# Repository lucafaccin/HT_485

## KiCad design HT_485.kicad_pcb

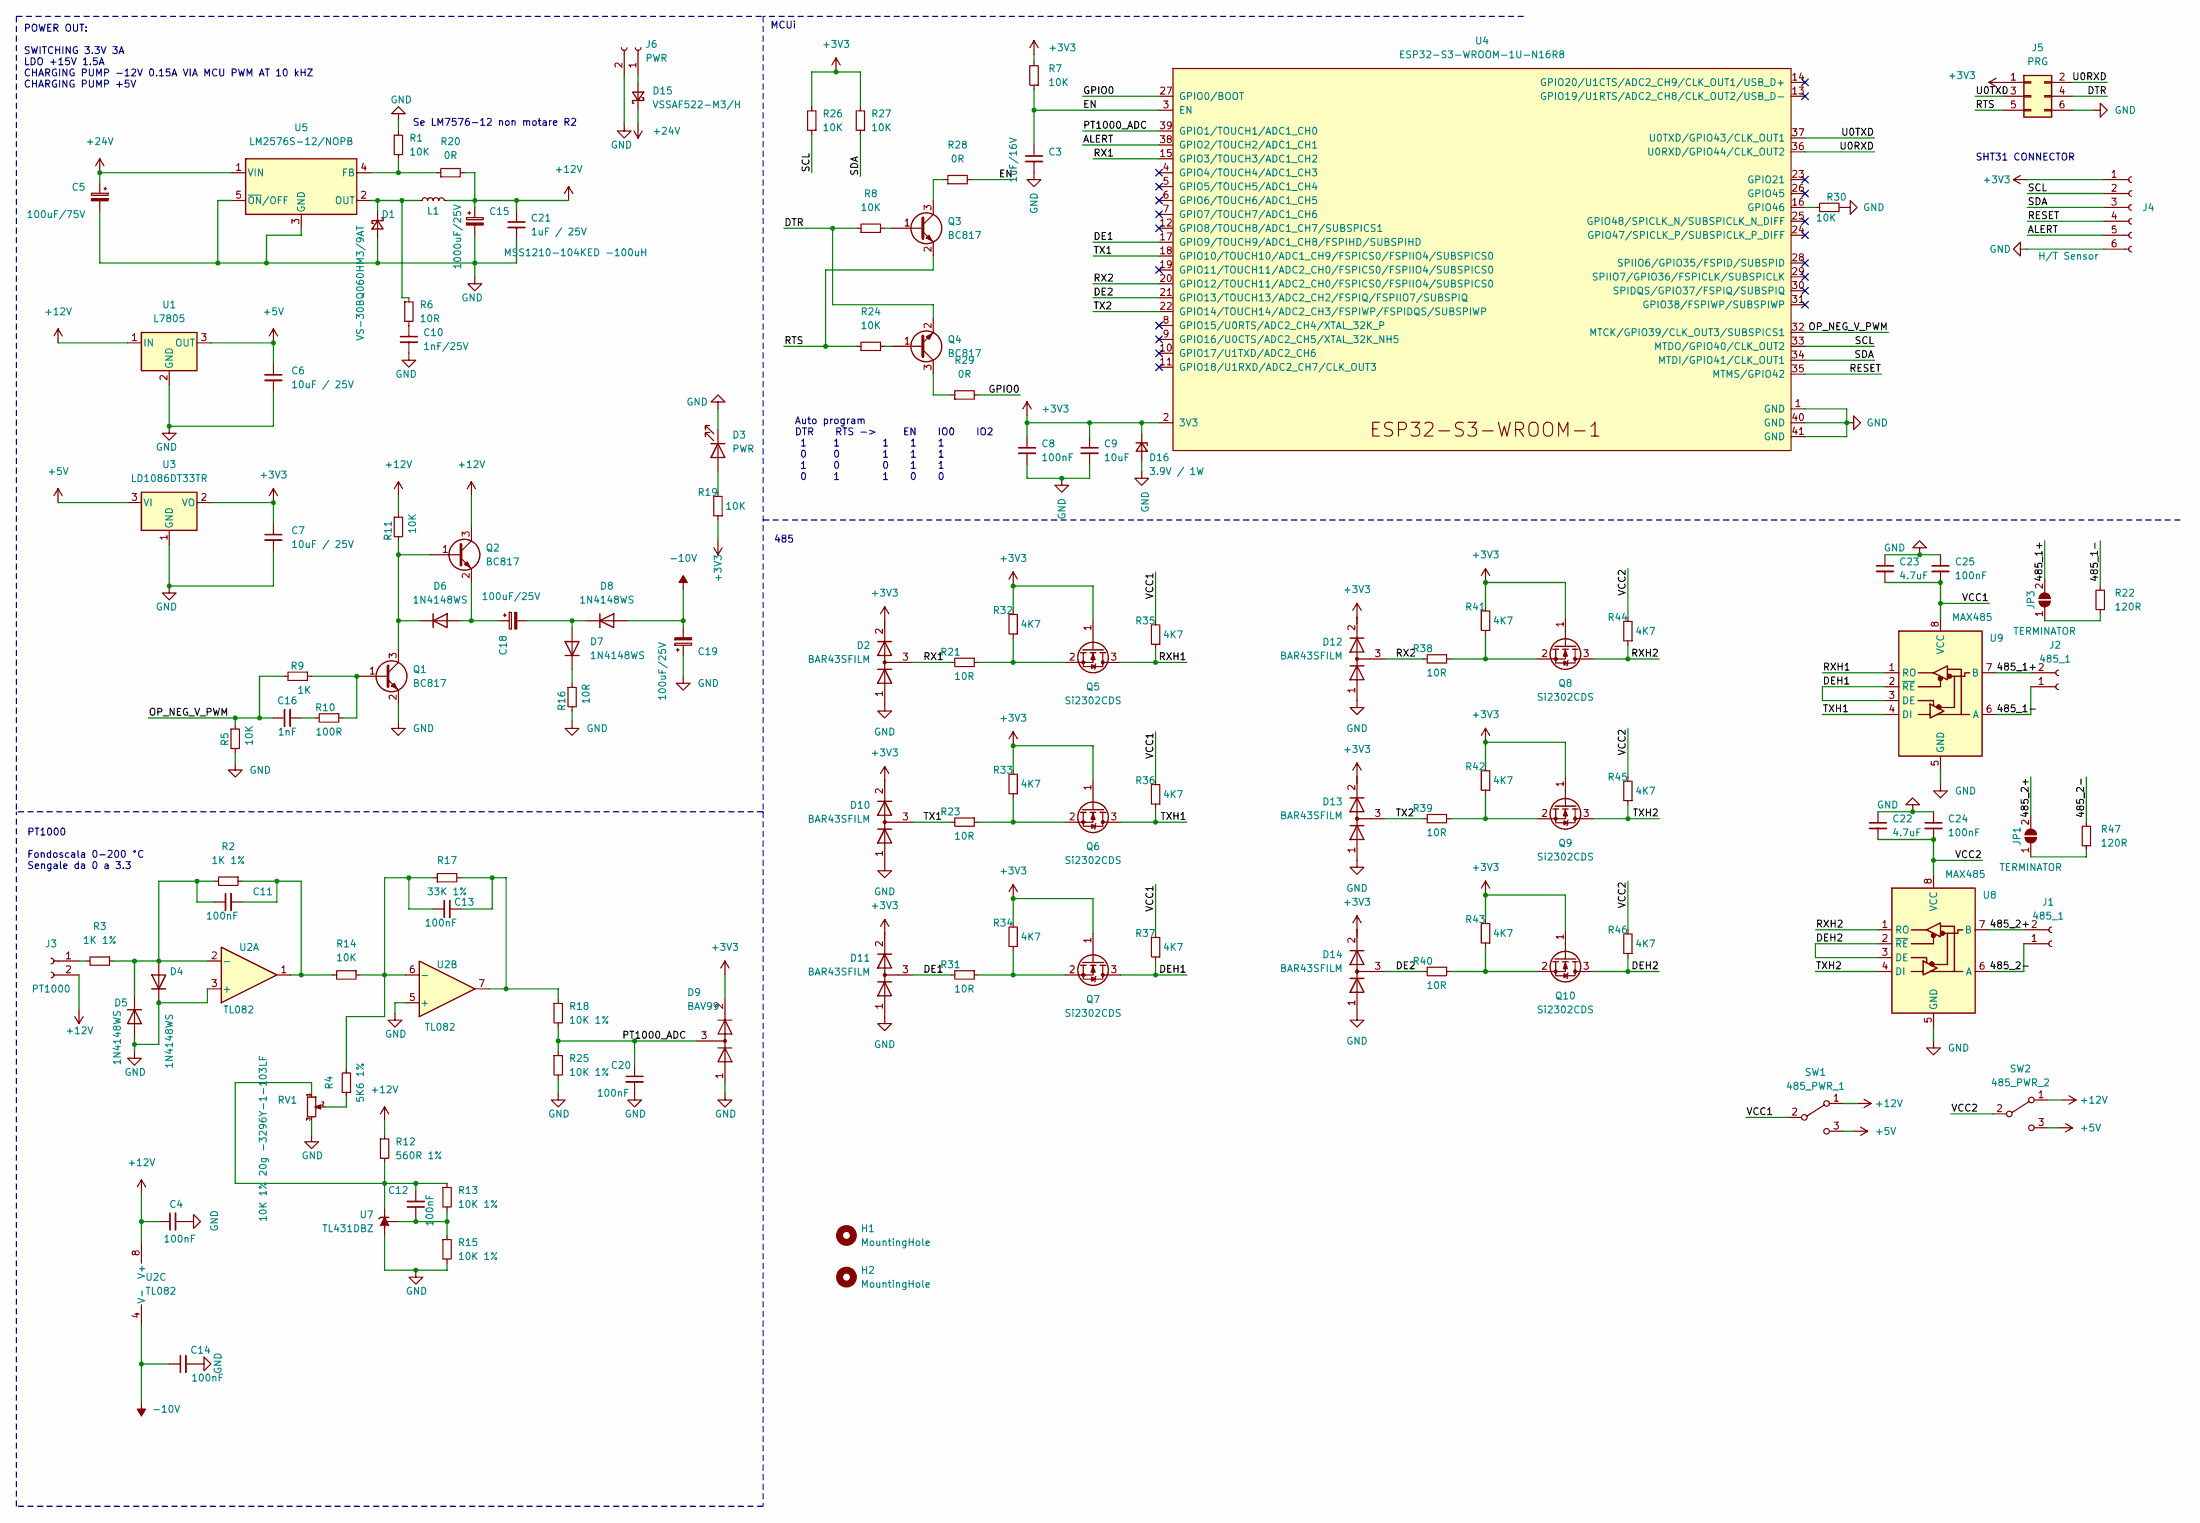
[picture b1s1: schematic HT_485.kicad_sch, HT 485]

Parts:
C3: 1uF/16V; C_0805_2012Metric
C4, C8, C11, C12, C13, C14, C20, C24, C25: 100nF; C_0805_2012Metric
C5: 100uF/75V; CP_Elec_8x10.5
C6, C7: 10uF / 25V; C_0805_2012Metric
C9: 10uF; C_0805_2012Metric
C10: 1nF/25V; C_0805_2012Metric
C15: 1000uF/25V; CP_Elec_10x10.5
C16: 1nF; C_0805_2012Metric
C18, C19: 100uF/25V; CP_Elec_6.3x7.7
C21: 1uF / 25V; C_0805_2012Metric
C22, C23: 4.7uF; C_0805_2012Metric
D1: VS-30BQ060HM3/9AT; D_SMB-SMC_Universal_Handsoldering
D2, D10, D11, D12, D13, D14: BAR43SFILM; SOT-23
D3: PWR; LED_0805_2012Metric
D4, D5, D6, D7, D8: 1N4148WS; D_SOD-323
D9: BAV99; SOT-23
D15: VSSAF522-M3/H; D_SMA-SMB_Universal_Handsoldering
D16: 3.9V / 1W; D_SOD-128
H1, H2: MountingHole; MountingHole_3.2mm_M3
J1, J2: 485_1; TerminalBlock_Phoenix_PT-1,5-2-5.0-H_1x02_P5.00mm_Horizontal
J3: PT1000; TerminalBlock_Phoenix_PT-1,5-2-3.5-H_1x02_P3.50mm_Horizontal
J4: H/T Sensor; JST_PH_S6B-PH-SM4-TB_1x06-1MP_P2.00mm_Horizontal
J5: PRG; PinSocket_2x03_P2.54mm_Vertical
J6: PWR; TerminalBlock_Phoenix_PT-1,5-2-5.0-H_1x02_P5.00mm_Horizontal
JP1, JP3: TERMINATOR; SolderJumper-2_P1.3mm_Open_RoundedPad1.0x1.5mm
L1: MSS1210-104KED -100uH; MSS1210-104KED
Q1, Q2, Q3, Q4: BC817; SOT-23
Q5, Q6, Q7, Q8, Q9, Q10: Si2302CDS; SOT-23
R1, R5, R7, R8, R11, R14, R19, R24, R26, R27, R30: 10K; R_0805_2012Metric_Pad1.20x1.40mm_HandSolder
R2, R3: 1K 1%; R_0805_2012Metric_Pad1.20x1.40mm_HandSolder
R4: 5K6 1%; R_0805_2012Metric_Pad1.20x1.40mm_HandSolder
R6, R16, R21, R23, R31, R38, R39, R40: 10R; R_0805_2012Metric_Pad1.20x1.40mm_HandSolder
R9: 1K; R_0805_2012Metric_Pad1.20x1.40mm_HandSolder
R10: 100R; R_0805_2012Metric_Pad1.20x1.40mm_HandSolder
R12: 560R 1%; R_0805_2012Metric_Pad1.20x1.40mm_HandSolder
R13, R15, R18, R25: 10K 1%; R_0805_2012Metric_Pad1.20x1.40mm_HandSolder
R17: 33K 1%; R_0805_2012Metric_Pad1.20x1.40mm_HandSolder
R20, R28, R29: 0R; R_0805_2012Metric_Pad1.20x1.40mm_HandSolder
R22, R47: 120R; R_0805_2012Metric_Pad1.20x1.40mm_HandSolder
R32, R33, R34, R35, R36, R37, R41, R42, R43, R44, R45, R46: 4K7; R_0805_2012Metric_Pad1.20x1.40mm_HandSolder
RV1: 10K 1% 20g -3296Y-1-103LF; Potentiometer_Bourns_3296Y_Vertical
SW1: 485_PWR_1; PinHeader_1x03_P2.54mm_Vertical
SW2: 485_PWR_2; PinHeader_1x03_P2.54mm_Vertical
U1: L7805; TO-252-3_TabPin2
U2: TL082; SOIC-8-1EP_3.9x4.9mm_P1.27mm_EP2.29x3mm
U3: LD1086DT33TR; TO-252-3_TabPin2
U4: ESP32-S3-WROOM-1U-N16R8; ESP32-S3-WROOM-1
U5: LM2576S-12/NOPB; TO-263-5_TabPin3
U7: TL431DBZ; SOT-23
U8, U9: MAX485; SOIC-8_3.9x4.9mm_P1.27mm

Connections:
+3V3: C7.1, C8.1, C9.1, D2.2 (K), D9.2 (A), D10.2 (K), D11.2 (K), D12.2 (K), D13.2 (K), D14.2 (K), D16.1 (K), J4.1, J5.1, Q5.1 (G), Q6.1 (G), Q7.1 (G), Q8.1 (G), Q9.1 (G), Q10.1 (G), R7.2, R19.1, R26.2, R27.2, R32.2, R33.2, R34.2, R41.2, R42.2, R43.2, U3.2 (VO), U4.2 (3V3)
+5V: C6.1, SW1.3 (C), SW2.3 (C), U1.3 (OUT), U3.3 (VI)
+12V: C4.1, C15.1, C21.1, J3.2, L1.2, Q2.3 (C), R11.1, R12.1, R20.2, SW1.1 (A), SW2.1 (A), U1.1 (IN), U2.8 (V+)
+24V: C5.1, D15.1 (K), U5.1 (VIN)
-10V: C14.1, C19.2, D8.2 (A), U2.4 (V-)
/485_1+: J2.2, JP3.2 (B), U9.7 (B)
/485_1-: J2.1, R22.2, U9.6 (A)
/485_2+: J1.2, JP1.2 (B), U8.7 (B)
/485_2-: J1.1, R47.2, U8.6 (A)
/ALERT: J4.5, U4.38 (GPIO2/TOUCH2/ADC1_CH1)
/DE1: D11.3 (common), R31.2, U4.17 (GPIO9/TOUCH9/ADC1_CH8/FSPIHD/SUBSPIHD)
/DE2: D14.3 (common), R40.2, U4.21 (GPIO13/TOUCH13/ADC2_CH2/FSPIQ/FSPIIO7/S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)
/DEH1: Q7.3 (D), R37.1, U9.2 (~RE), U9.3 (DE)
/DEH2: Q10.3 (D), R46.1, U8.2 (~RE), U8.3 (DE)
/DTR: J5.4, Q4.2 (E), R8.1
/EN: C3.1, R7.1, R28.2, U4.3 (EN)
/GPIO0: R29.2, U4.27 (GPIO0/BOOT)
/OP_NEG_V_PWM: C16.1, R5.1, R9.2, U4.32 (MTCK/GPIO39/CLK_OUT3/SUBSPICS1)
/PT1000_ADC: C20.1, D9.3 (K), R18.2, R25.1, U4.39 (GPIO1/TOUCH1/ADC1_CH0)
/RESET: J4.4, U4.35 (MTMS/GPIO42)
/RTS: J5.5, Q3.2 (E), R24.1
/RX1: D2.3 (common), R21.2, U4.15 (GPIO3/TOUCH3/ADC1_CH2)
/RX2: D12.3 (common), R38.2, U4.20 (GPIO12/TOUCH11/ADC2_CH0/FSPICS0/FSPIIO4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)
/RXH1: Q5.3 (D), R35.1, U9.1 (RO)
/RXH2: Q8.3 (D), R44.1, U8.1 (RO)
/SCL: J4.2, R26.1, U4.33 (MTDO/GPIO40/CLK_OUT2)
/SDA: J4.3, R27.1, U4.34 (MTDI/GPIO41/CLK_OUT1)
/TX1: D10.3 (common), R23.2, U4.18 (GPIO10/TOUCH10/ADC1_CH9/FSPICS0/FSPIIO4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)
/TX2: D13.3 (common), R39.2, U4.22 (GPIO14/TOUCH14/ADC2_CH3/FSPIWP/FSPIDQS/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)
/TXH1: Q6.3 (D), R36.1, U9.4 (DI)
/TXH2: Q9.3 (D), R45.1, U8.4 (DI)
/U0RXD: J5.2, U4.36 (U0RXD/GPIO44/CLK_OUT2)
/U0TXD: J5.3, U4.37 (U0TXD/GPIO43/CLK_OUT1)
/VCC1: C23.2, C25.2, R35.2, R36.2, R37.2, SW1.2 (B), U9.8 (VCC)
/VCC2: C22.2, C24.2, R44.2, R45.2, R46.2, SW2.2 (B), U8.8 (VCC)
GND: C3.2, C4.2, C5.2, C6.2, C7.2, C8.2, C9.2, C10.2, C14.2, C15.2, C19.1, C20.2, C21.2, C22.1, C23.1, C24.1, C25.1, D1.2 (A), D2.1 (A), D3.1 (K), D4.1 (K), D5.2 (A), D9.1 (K), D10.1 (A), D11.1 (A), D12.1 (A), D13.1 (A), D14.1 (A), D16.2 (A), J4.6, J5.6, J6.2, Q1.2 (E), R1.1, R5.2, R15.2, R16.2, R25.2, R30.2, RV1.3, U1.2 (GND), U2.3 (+), U2.5 (+), U3.1 (GND), U4.1 (GND), U4.40 (GND), U4.41 (GND), U5.3 (GND), U5.5 (~ON/OFF), U7.3 (A), U8.5 (GND), U9.5 (GND)
unnamed: C10.1, R6.2
unnamed: C11.2, R2.1, R14.2, U2.1
unnamed: C13.2, R17.2, R18.1, U2.7
unnamed: C16.2, R10.2
unnamed: D1.1 (K), L1.1, R6.1, U5.2 (OUT)
unnamed: D3.2 (A), R19.2
unnamed: C11.1, D4.2 (A), D5.1 (K), R2.2, R3.1, U2.2 (-)
unnamed: C18.1, D6.2 (A), Q2.2 (E)
unnamed: D6.1 (K), Q1.3 (C), Q2.1 (B), R11.2
unnamed: C18.2, D7.2 (A), D8.1 (K)
unnamed: D7.1 (K), R16.1
unnamed: D15.2 (A), J6.1
unnamed: J3.1, R3.2
unnamed: JP1.1 (A), R47.1
unnamed: JP3.1 (A), R22.1
unnamed: Q1.1 (B), R9.1, R10.1
unnamed: Q3.1 (B), R8.2
unnamed: Q3.3 (C), R28.1
unnamed: Q4.1 (B), R24.2
unnamed: Q4.3 (C), R29.1
unnamed: Q5.2 (S), R21.1, R32.1
unnamed: Q6.2 (S), R23.1, R33.1
unnamed: Q7.2 (S), R31.1, R34.1
unnamed: Q8.2 (S), R38.1, R41.1
unnamed: Q9.2 (S), R39.1, R42.1
unnamed: Q10.2 (S), R40.1, R43.1
unnamed: R4.1, RV1.2
unnamed: C13.1, R4.2, R14.1, R17.1, U2.6 (-)
unnamed: R30.1, U4.16 (GPIO46)
unnamed: R1.2, R20.1, U5.4 (FB)
unnamed: C12.2, R12.2, R13.1, RV1.1, U7.1 (K)
unnamed: C12.1, R13.2, R15.1, U7.2 (REF)

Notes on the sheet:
Auto program DTR RTS -> EN IO0 IO2 1 1 1 1 1 0 0 1 1 1 1 0 0 1 1 0 1 1 0 0
485
Se LM7576-12 non motare R2
SHT31 CONNECTOR
MCUì
PT1000 Fondoscala 0-200 °C Sengale da 0 a 3.3
POWER OUT: SWITCHING 3.3V 3A LDO +15V 1.5A CHARGING PUMP -12V 0.15A VIA MCU PWM AT 10 kHZ CHARGING PUMP +5V

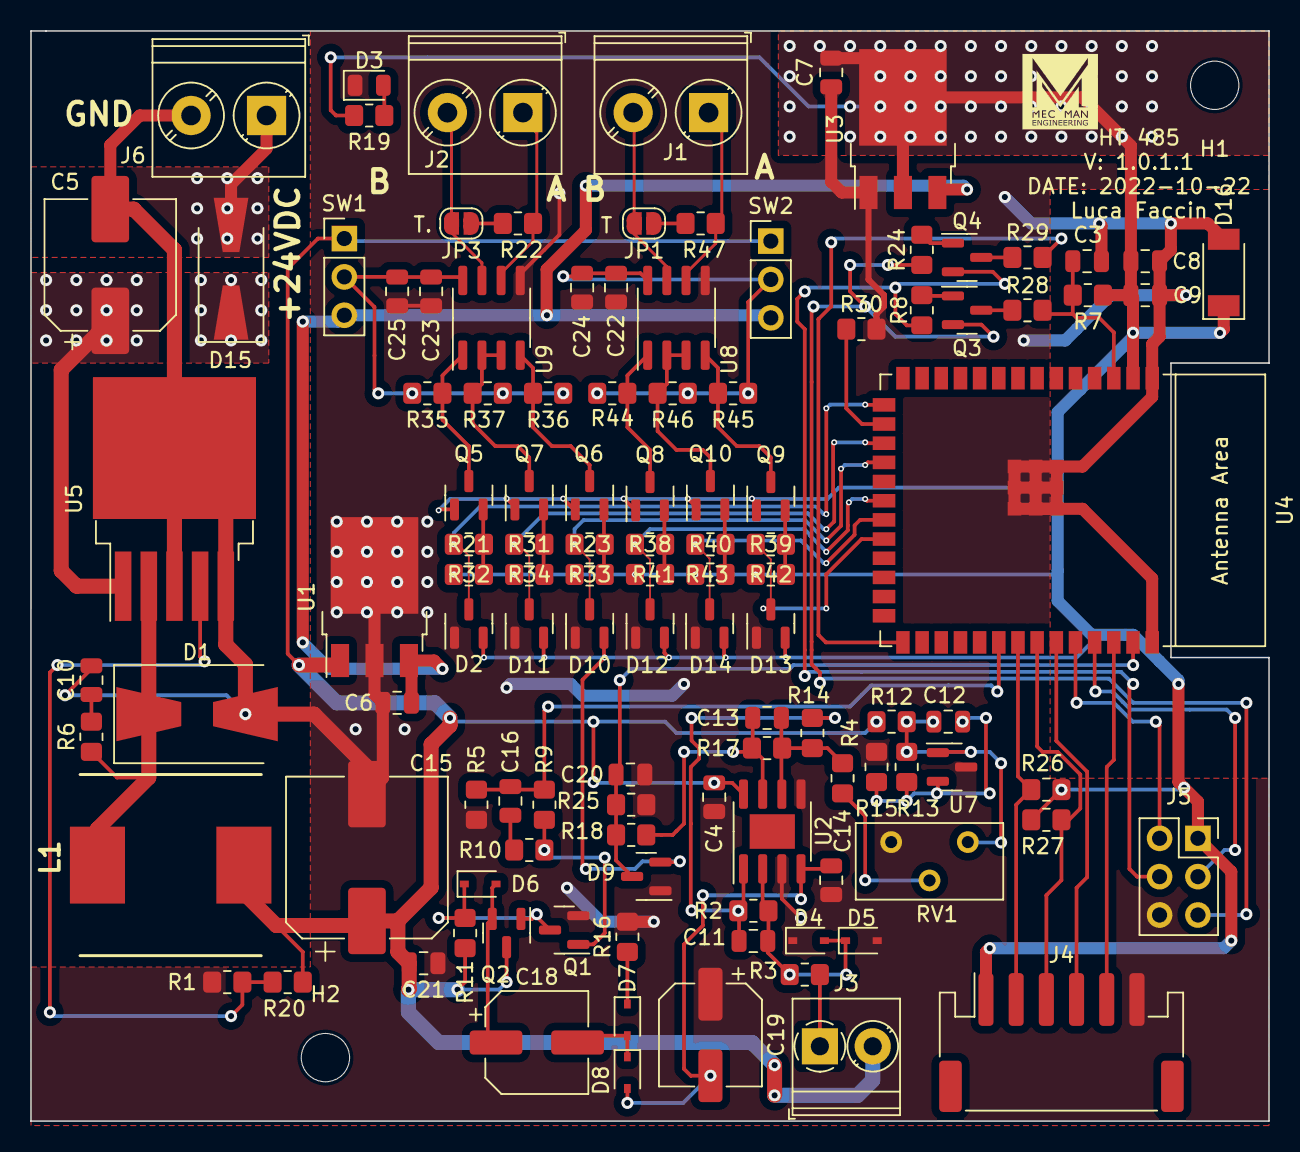
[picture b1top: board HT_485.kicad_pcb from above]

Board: 2 copper layers, 82.0 x 72.2 mm, 117 parts (0 on the bottom side), 68 nets.

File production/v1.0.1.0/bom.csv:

Designator,Footprint,Quantity,Value,LCSC Part #
C10,C_0805_2012Metric,1,1nF/25V,
"C11, C12, C13, C14, C20, C24, C25, C4, C8",C_0805_2012Metric,9,100nF,
C15,CP_Elec_10x10.5,1,1000uF/25V,
C16,C_0805_2012Metric,1,1nF,
"C18, C19",CP_Elec_6.3x7.7,2,100uF/25V,
C21,C_0805_2012Metric,1,1uF / 25V,
"C22, C23",C_0805_2012Metric,2,4.7uF,
C3,C_0805_2012Metric,1,1uF/16V,
C5,CP_Elec_8x10.5,1,100uF/75V,
"C6, C7",C_0805_2012Metric,2,10uF / 25V,
C9,C_0805_2012Metric,1,10uF,
D1,D_SMB-SMC_Universal_Handsoldering,1,VS-30BQ060HM3/9AT,
"D10, D11, D12, D13, D14, D2",SOT-23,6,BAR43SFILM,
D15,D_SMA-SMB_Universal_Handsoldering,1,VSSAF522-M3/H,
D16,D_SOD-128,1,3.9V / 1W,
D3,LED_0805_2012Metric,1,PWR,
"D4, D5, D6, D7, D8",D_SOD-323,5,1N4148WS,
D9,SOT-23,1,BAV99,
"H1, H2",MountingHole_3.2mm_M3,2,MountingHole,
"J1, J2","TerminalBlock_Phoenix_PT-1,5-2-3.5-H_1x02_P3.50mm_Horizontal",2,485_1,
J3,"TerminalBlock_Phoenix_PT-1,5-2-3.5-H_1x02_P3.50mm_Horizontal",1,PT1000,
J4,JST_PH_S6B-PH-SM4-TB_1x06-1MP_P2.00mm_Horizontal,1,H/T Sensor,
J5,PinSocket_2x03_P2.54mm_Vertical,1,PRG,
J6,"TerminalBlock_Phoenix_PT-1,5-2-5.0-H_1x02_P5.00mm_Horizontal",1,PWR,
"JP1, JP3",SolderJumper-2_P1.3mm_Open_RoundedPad1.0x1.5mm,2,TERMINATOR,
L1,MSS1210-104KED,1,MSS1210-104KED -100uH,
"Q1, Q2, Q3, Q4",SOT-23,4,BC817,
"Q10, Q5, Q6, Q7, Q8, Q9",SOT-23,6,Si2302CDS,
"R1, R11, R14, R19, R24, R26, R27, R30, R5, R7, R8",R_0805_2012Metric_Pad1.20x1.40mm_HandSolder,11,10K,
R10,R_0805_2012Metric_Pad1.20x1.40mm_HandSolder,1,100R,
R12,R_0805_2012Metric_Pad1.20x1.40mm_HandSolder,1,560R 1%,
"R13, R15, R18, R25",R_0805_2012Metric_Pad1.20x1.40mm_HandSolder,4,10K 1%,
"R16, R21, R23, R31, R38, R39, R40, R6",R_0805_2012Metric_Pad1.20x1.40mm_HandSolder,8,10R,
R17,R_0805_2012Metric_Pad1.20x1.40mm_HandSolder,1,33K 1%,
"R2, R3",R_0805_2012Metric_Pad1.20x1.40mm_HandSolder,2,1K 1%,
"R20, R28, R29",R_0805_2012Metric_Pad1.20x1.40mm_HandSolder,3,0R,
"R22, R47",R_0805_2012Metric_Pad1.20x1.40mm_HandSolder,2,120R,
"R32, R33, R34, R35, R36, R37, R41, R42, R43, R44, R45, R46",R_0805_2012Metric_Pad1.20x1.40mm_HandSolder,12,4K7,
R4,R_0805_2012Metric_Pad1.20x1.40mm_HandSolder,1,5K6 1%,
R9,R_0805_2012Metric_Pad1.20x1.40mm_HandSolder,1,1K,
RV1,Potentiometer_Bourns_3296Y_Vertical,1,10K 1% 20g -3296Y-1-103LF,
SW1,PinHeader_1x03_P2.54mm_Vertical,1,485_PWR_1,
SW2,PinHeader_1x03_P2.54mm_Vertical,1,485_PWR_2,
U1,TO-252-3_TabPin2,1,L7805,
U2,SOIC-8-1EP_3.9x4.9mm_P1.27mm_EP2.29x3mm,1,TL082,
U3,TO-252-3_TabPin2,1,LD1086DT33TR,
U4,ESP32-S3-WROOM-1,1,ESP32-S3-WROOM-1U-N16R8,
U5,TO-263-5_TabPin3,1,LM2576S-12/NOPB,
U7,SOT-23,1,TL431DBZ,
"U8, U9",SOIC-8_3.9x4.9mm_P1.27mm,2,MAX485,

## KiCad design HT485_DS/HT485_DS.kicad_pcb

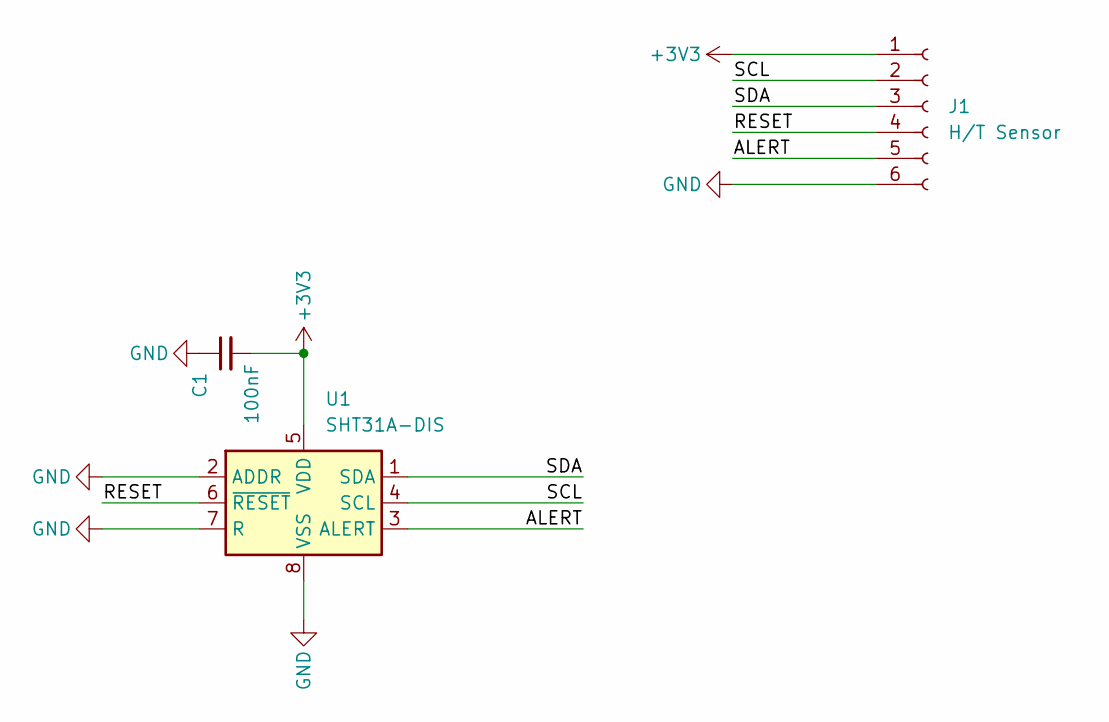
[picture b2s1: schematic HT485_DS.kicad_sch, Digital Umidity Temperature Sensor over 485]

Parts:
C1: 100nF; C_0805_2012Metric
J1: H/T Sensor; JST_PH_B6B-PH-K_1x06_P2.00mm_Vertical
U1: SHT31A-DIS; Sensirion_DFN-8-1EP_2.5x2.5mm_P0.5mm_EP1.1x1.7mm

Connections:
+3V3: C1.2, J1.1, U1.5 (VDD)
/ALERT: J1.5, U1.3 (ALERT)
/RESET: J1.4, U1.6 (~RESET)
/SCL: J1.2, U1.4 (SCL)
/SDA: J1.3, U1.1 (SDA)
GND: C1.1, J1.6, U1.2 (ADDR), U1.7 (R), U1.8 (VSS), U1.9 (VSS)

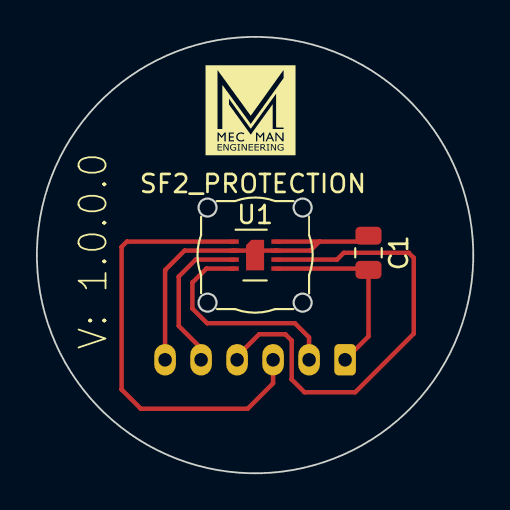
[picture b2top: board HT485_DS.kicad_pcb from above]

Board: 2 copper layers, 24.2 x 24.2 mm, 4 parts (1 on the bottom side), 6 nets.

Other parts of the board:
SF2_PROTECTION: SF2

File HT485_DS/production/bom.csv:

Designator,Footprint,Quantity,Value,LCSC Part #
C1,C_0805_2012Metric,1,100nF,
J1,JST_PH_B6B-PH-K_1x06_P2.00mm_Vertical,1,H/T Sensor,
SF2_PROTECTION,SF2,1,SF2,
U1,Sensirion_DFN-8-1EP_2.5x2.5mm_P0.5mm_EP1.1x1.7mm,1,SHT31A-DIS,

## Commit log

2022-07-07 Lavoro terminato
2022-07-08 Adattato master a scatola
2022-07-08 Modificata posizione resistenze
2022-07-08 Rimossi file non utili
2022-07-11 Aggiunto terminatore 485
2022-07-12 Aggiunti 3D Sensori
2022-07-12 Rivisti dip switch con solder jumper
2022-07-13 Messa pompa di carica per 485 a 5V
2022-09-09 Revisione 1.0.0.0 con PT1000
2022-09-12 Cambiata traccia per 3v3 e alimentatore switching
2022-10-06 Remaster
2022-10-08 Sistemate resistenze di centratura PT1000
2022-10-08 Aggiunto progetto Sensore i2C
2022-10-08 Fatta scheda sensore
2022-10-08 Aggiornato gerber
2022-10-10 Provato cambio resistenze operazionali. NULLA
2022-10-11 Ancora problemi PT1000
2022-10-14 Rimosso piano di massa da sensore T/H digitale Aggiunti dati per produzione JLCPCB
2022-10-16 Rivisto completamente PT1000 ingresso
2022-10-17 Rifatto schema 485. Master da rifare
2022-10-17 Rivisto tutta la scheda
2022-10-17 Aggiunto diodo per alimentazione CPU
2022-10-17 Correto mosfet voltage shifter.
2022-10-22 Revisionato master
2022-10-22 Aggiunti logo MME. Versione 1.0.1.0
2024-10-04 Messi connettori 485 a passo 5. Aggiornata versione a 1.0.1.1
